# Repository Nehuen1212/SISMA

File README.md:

#  SISMA: Simulador Interactivo de Sismos para Maquetas y Análisis

##  Resumen Ejecutivo del Proyecto

SISMA (Simulador Interactivo de Sismos para Maquetas y Análisis) surge como la respuesta a una de las problemáticas fundamentales en la arquitectura y la ingeniería civil: **la estabilidad de las estructuras ante fenómenos sísmicos**. El proyecto plantea una solución innovadora para la **prueba y el análisis a escala** de diseños estructurales frente a dichos eventos naturales.

SISMA se centra en la fabricación de un **simulador de sismos a escala** que permite a los usuarios:

* **Probar la estabilidad de maquetas** de edificios o estructuras.
* **Observar la reacción en tiempo real** ante distintos tipos de movimientos sísmicos.

El simulador está diseñado para **reproducir movimientos sísmicos reales** en una base móvil de alta precisión, garantizando un entorno de prueba realista y controlable.

***

##  Impacto y Valor Educativo

SISMA trasciende la mera simulación; es una **herramienta educativa** fundamental:

| Aspecto | Descripción |
| :--- | :--- |
| **Análisis Directo** | Permite observar cómo distintos diseños resisten o fallan, facilitando la variación de parámetros y la identificación de puntos débiles. |
| **Principios Fundamentales** | Demuestra de forma práctica por qué un diseño estructural bien pensado es esencial, ilustrando cómo pequeñas decisiones en la construcción pueden definir la diferencia entre la **estabilidad** y el **colapso**. |
| **Usabilidad** | El dispositivo ha sido diseñado para ser **intuitivo** y estar listo para su uso, eliminando la necesidad de interfaces complejas. |

### Audiencia Objetivo

* **Estudiantes de Arquitectura:** Para la validación práctica de sus proyectos y diseños.
* **Escuelas Técnicas y Facultades de Ingeniería:** Como recurso didáctico avanzado.
* **Ferias y Espacios Educativos:** Para informar y concienciar a futuros profesionales sobre las amenazas naturales.

***

## 💻 Código Fuente y Componentes Técnicos

Este repositorio alberga el código fuente necesario para el funcionamiento completo de SISMA, segmentado en tres áreas principales:

1.  ** Código Original del GRBL (Modificado):**
    * Incluye el **firmware GRBL** con las modificaciones específicas requeridas para la **adaptación** y el control de movimiento del prototipo de SISMA.

2.  ** Código de Sensado MPU6050:**
    * Contiene el código optimizado para la lectura y el procesamiento de datos del sensor **MPU6050** (Giroscopio y Acelerómetro), vital para el análisis del movimiento de la maqueta.

3.  ** Código Fuente de Interfaz y Control:**
    * Comprende el código de la **interfaz de usuario** utilizada para el control del simulador y la **generación de sismos en formato GCODE**.

4. ** Planos y piezas:**
    * Contiene todas las piezas del prototipo con sus respectivos planos y modelos en .STEP, STL o como proyecto de FreeCad para su posterior modificación, fabricación y montaje**.

***

##  Instalación y Uso
Para el uso de este repositorio es necesario cargar el firmaware del GRBL en un **ESP32** con su respectivo **SHIELD SISMA**. Luego deben descargarse e instalarse los controladores del prototipo que contienen tanto la ejecución como generación de sismos mediante G-CODE.
Por último para el montaje del prototipo deben fabricarse/imprimirse todas las piezas y seguir correctamente el montaje como lo indica la documentación presente en actual repositorio.

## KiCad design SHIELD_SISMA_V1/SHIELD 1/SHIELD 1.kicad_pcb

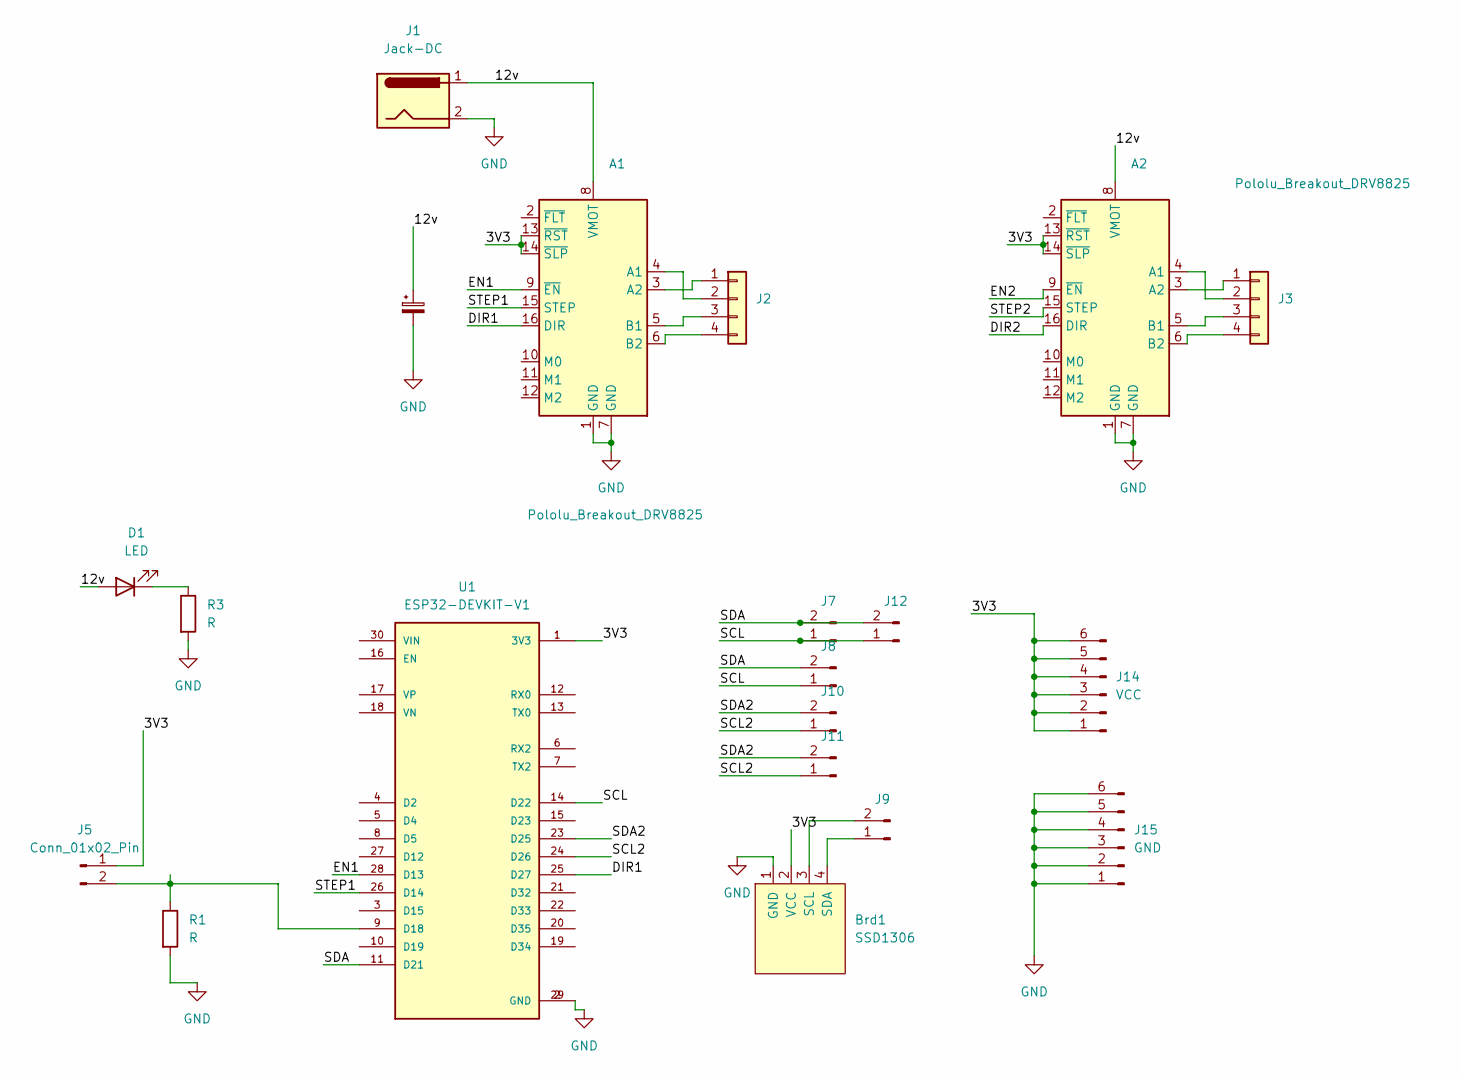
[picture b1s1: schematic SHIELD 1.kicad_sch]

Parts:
A1, A2: Pololu_Breakout_DRV8825; Pololu_Breakout-16_15.2x20.3mm
Brd1: SSD1306; 128x64OLED
C2: C_Polarized_Small; CP_Radial_D8.0mm_P5.00mm
D1: LED; LED_D5.0mm
J1: Jack-DC; BarrelJack_Horizontal
J2, J3: Conn_01x04; TerminalBlock_Phoenix_MKDS-1,5-4-5.08_1x04_P5.08mm_Horizont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
J5: Conn_01x02_Pin; TerminalBlock_Phoenix_MKDS-1,5-2-5.08_1x02_P5.08mm_Horizont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
J7, J8, J9, J10, J11, J12: Conn_01x02_Pin; PinHeader_2x01_P2.54mm_Vertical
J14: VCC; PinHeader_2x03_P2.54mm_Vertical
J15: GND; PinHeader_2x03_P2.54mm_Vertical
R1, R3: R; R_Axial_DIN0207_L6.3mm_D2.5mm_P7.62mm_Horizontal
U1: ESP32-DEVKIT-V1; MODULE_ESP32_DEVKIT_V1; PARTREV N/A

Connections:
/3V3: A1.13 (~RST), A1.14 (~SLP), A2.13 (~RST), A2.14 (~SLP), Brd1.2 (VCC), J5.1, J14.1, J14.2, J14.3, J14.4, J14.5, J14.6, U1.1 (3V3)
/12v: A1.8 (VMOT), A2.8 (VMOT), C2.1, D1.2 (A), J1.1
/DIR1: A1.16 (DIR), U1.25 (D27)
/EN1: A1.9 (~EN), U1.28 (D13)
/SCL: J7.1, J8.1, J12.1, U1.14 (D22)
/SCL2: J10.1, J11.1, U1.24 (D26)
/SDA: J7.2, J8.2, J12.2, U1.11 (D21)
/SDA2: J10.2, J11.2, U1.23 (D25)
/STEP1: A1.15 (STEP), U1.26 (D14)
GND: A1.1 (GND), A1.7 (GND), A2.1 (GND), A2.7 (GND), Brd1.1 (GND), C2.2, J1.2, J15.1, J15.2, J15.3, J15.4, J15.5, J15.6, R1.2, R3.2, U1.2 (GND), U1.29 (GND)
unnamed: A1.4 (A1), J2.2
unnamed: A1.3 (A2), J2.1
unnamed: A1.5 (B1), J2.3
unnamed: A1.6 (B2), J2.4
unnamed: A2.3 (A2), J3.1
unnamed: A2.4 (A1), J3.2
unnamed: A2.5 (B1), J3.3
unnamed: A2.6 (B2), J3.4
unnamed: Brd1.3 (SCL), J9.2
unnamed: Brd1.4 (SDA), J9.1
unnamed: D1.1 (K), R3.1
unnamed: J5.2, R1.1, U1.9 (D18)

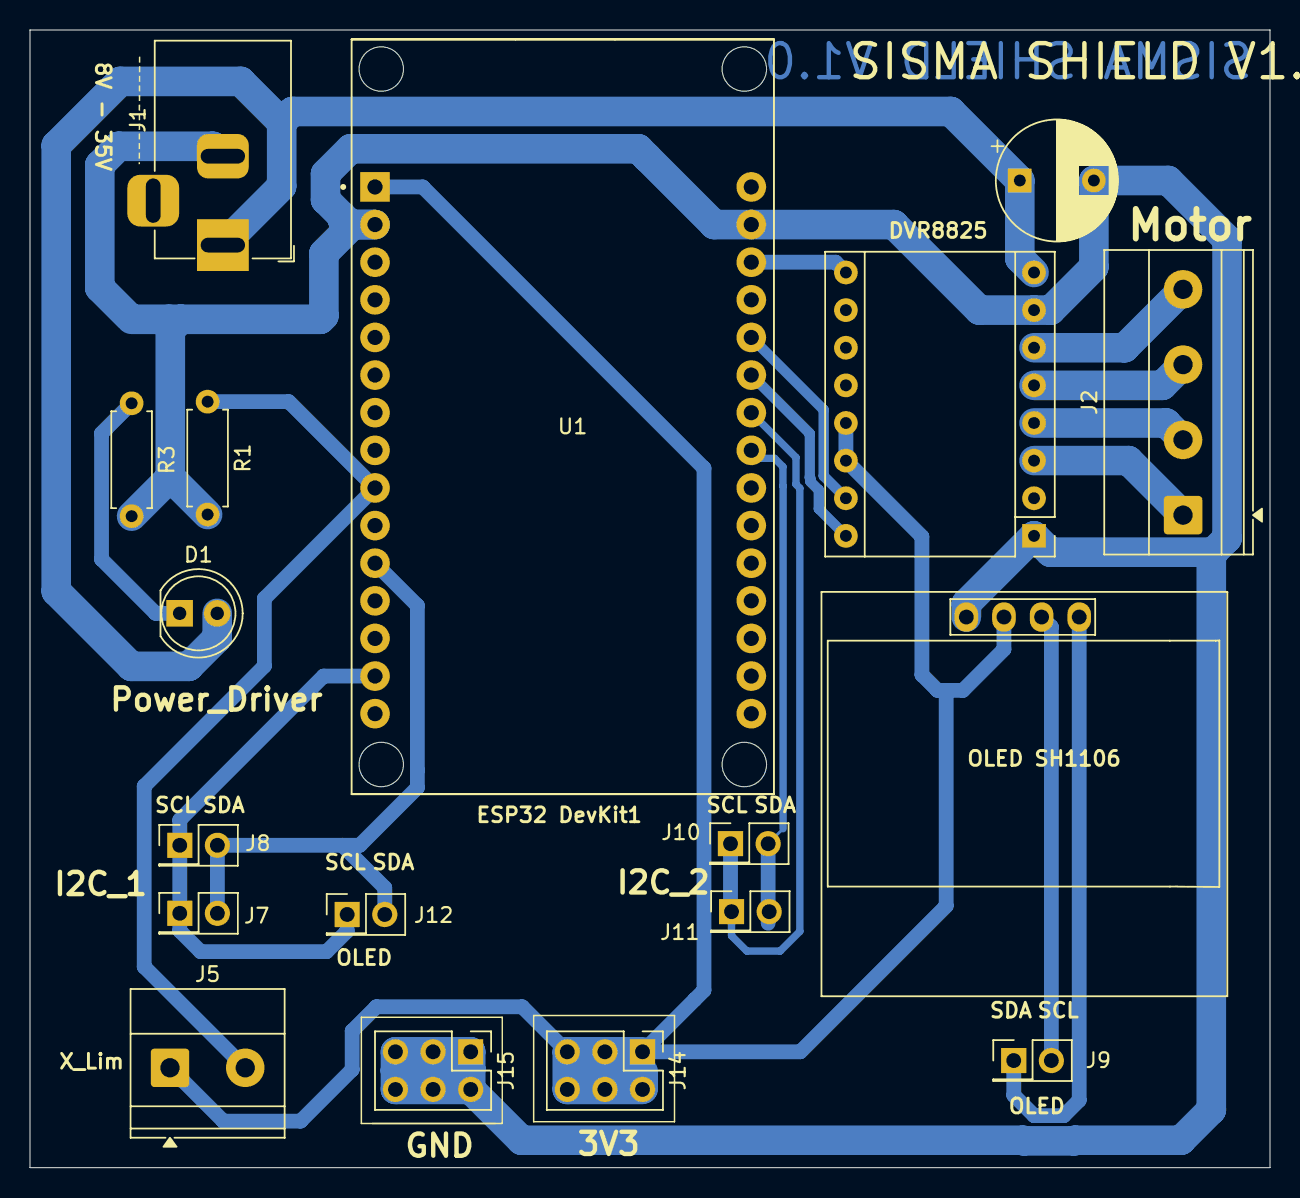
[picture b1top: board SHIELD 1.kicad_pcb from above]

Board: 2 copper layers, 83.7 x 76.8 mm, 18 parts (0 on the bottom side), 18 nets.

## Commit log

2025-10-25 Update README.md for clarity and formatting
    Corrected formatting and added emphasis to project descriptions.
2025-10-25 Correct formatting in README.md
    Fixed formatting issues in the README file.
2025-10-25 Fix formatting issues in README.md
2025-10-25 Update README with project details
    Added description of original GRBL code and MPU6050 sensor code.
2025-10-25 Upload GRBL - Initial commit
2025-10-25 Upload README
2025-10-25 Update README and Upload CAD Models
2025-10-25 Update CAD Models
2025-10-25 Upload SISMA_CONTROLADOR python project and .exe
2025-10-26 Upload Sensado
2025-10-30 Upload SHIELD
